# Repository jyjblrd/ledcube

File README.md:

# ledcube
Details: [https://www.joshuabird.com/blog/post/rgb-led-cube](https://www.joshuabird.com/blog/post/rgb-led-cube)

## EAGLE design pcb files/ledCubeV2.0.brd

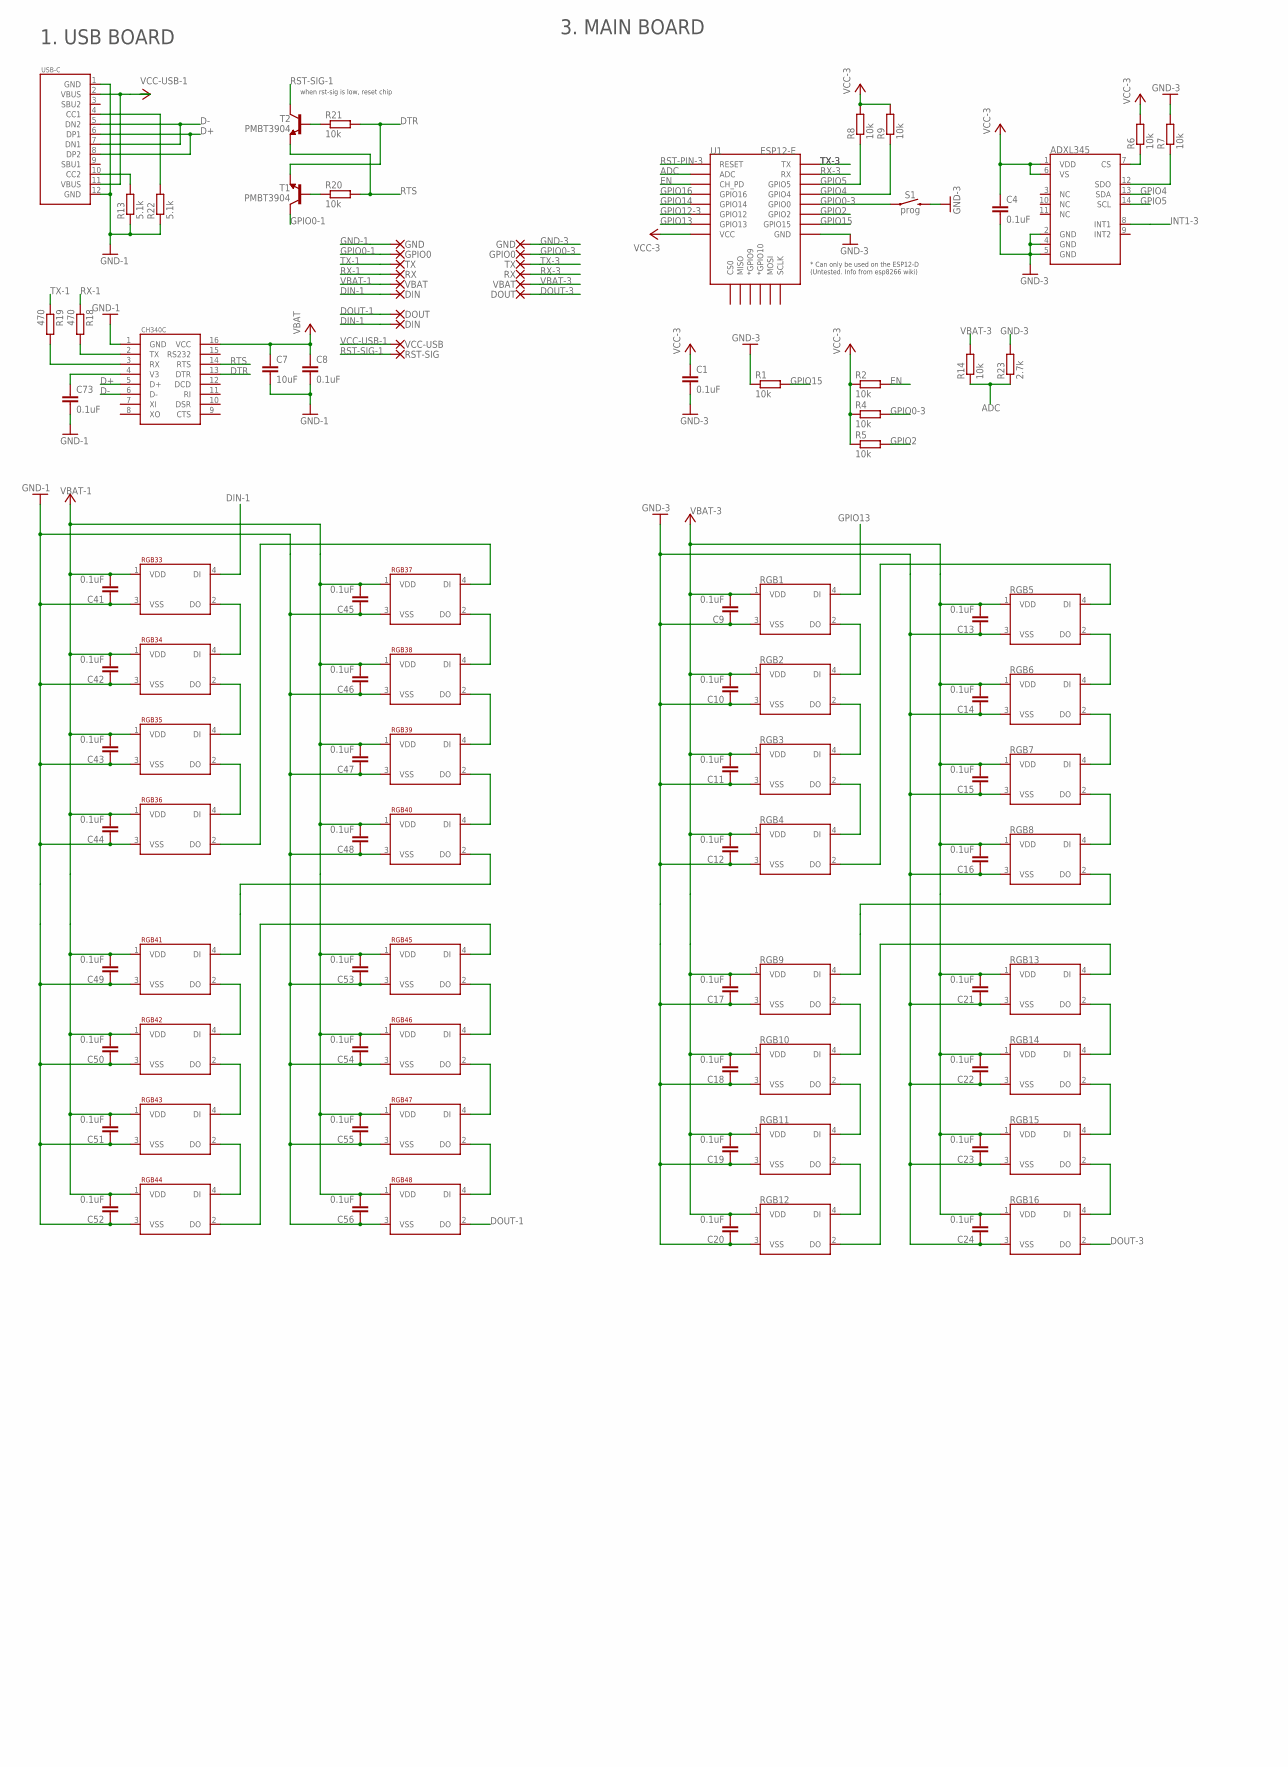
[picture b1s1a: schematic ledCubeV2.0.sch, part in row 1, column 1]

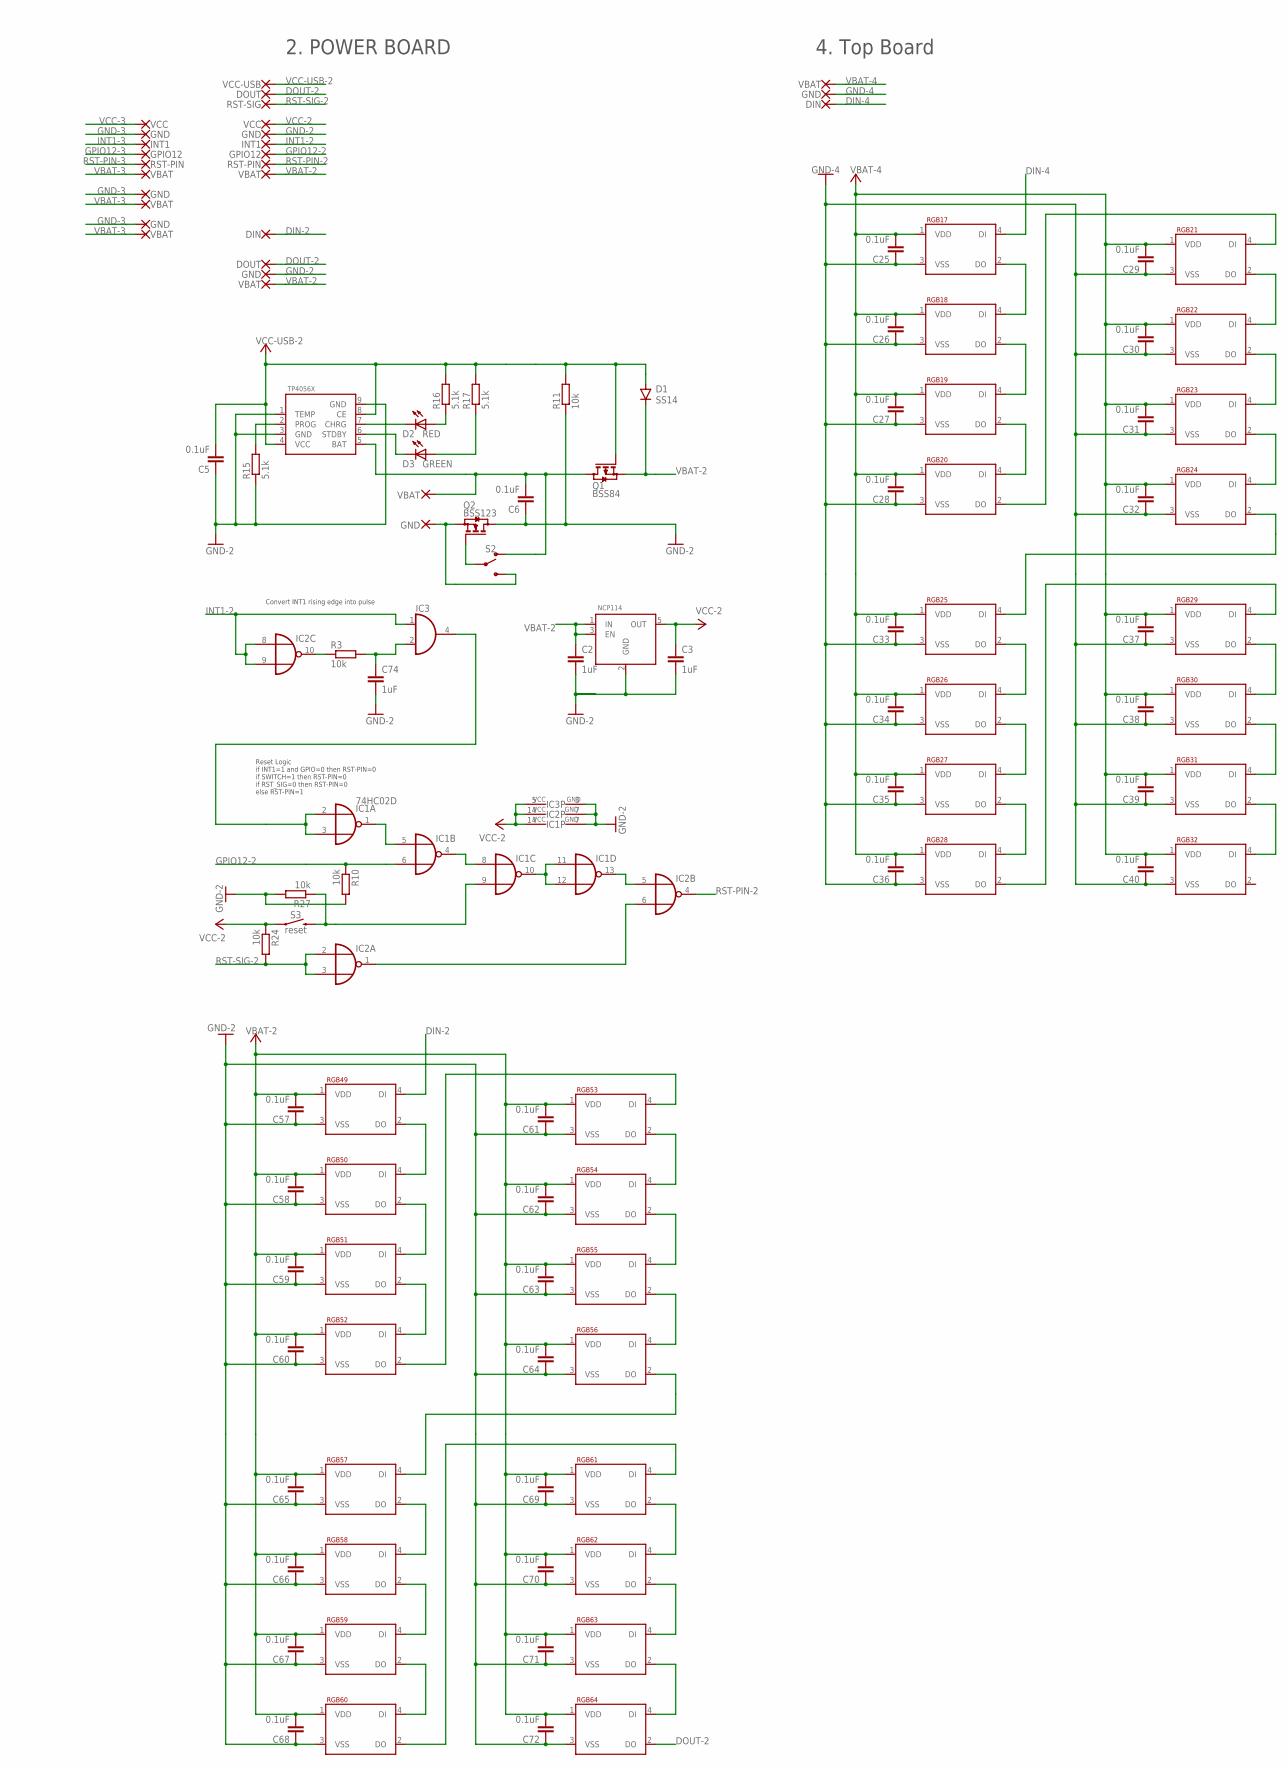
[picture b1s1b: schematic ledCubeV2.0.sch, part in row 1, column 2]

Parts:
ADXL345: ADXL345; LGA-14
C1, C4, C5, C6, C8, C9, C10, C11, C12, C13, C14, C15, C16, C17, C18, C19, C20, C21, C22, C23, C24, C25, C26, C27, C28, C29, C30, C31, C32, C33, C34, C35, C36, C37, C38, C39, C40, C41, C42, C43, C44, C45, C46, C47, C48, C49, C50, C51, C52, C53, C54, C55, C56, C57, C58, C59, C60, C61, C62, C63, C64, C65, C66, C67, C68, C69, C70, C71, C72, C73: 0.1uF; C0603
C2, C3, C74: 1uF; C0603
C7: 10uF; C0603
CH340C: CH340G; SOIC16
D1: SS14; DO-214AC
D2: RED; LED_SML0603
D3: GREEN; LED_SML0603
GND: SMD2; SMD1,27-2,54
GND-1: GND; SMD1,27-2,54
GND-2: RX; SMD1,27-2,54
GPIO0-1, GPIO0-2: GPIO0; SMD1,27-2,54
IC1, IC2: 74HC02D; SO14
IC3: 74AHC1G08DCK; SC70-5
NCP114: NCP114; TSOP-5
Q1: BSS84; SOT23
Q2: BSS123; SOT23
R1, R2, R3, R4, R5, R6, R7, R8, R9, R10, R11, R14, R20, R21, R24, R27: 10k; R0603
R13, R15, R16, R17, R22: 5.1k; R0603
R18, R19: 470; R0603
R23: 2.7k; R0603
RGB1, RGB2, RGB3, RGB4, RGB5, RGB6, RGB7, RGB8, RGB9, RGB10, RGB11, RGB12, RGB13, RGB14, RGB15, RGB16, RGB17, RGB18, RGB19, RGB20, RGB21, RGB22, RGB23, RGB24, RGB25, RGB26, RGB27, RGB28, RGB29, RGB30, RGB31, RGB32, RGB33, RGB34, RGB35, RGB36, RGB37, RGB38, RGB39, RGB40, RGB41, RGB42, RGB43, RGB44, RGB45, RGB46, RGB47, RGB48, RGB49, RGB50, RGB51, RGB52, RGB53, RGB54, RGB55, RGB56, RGB57, RGB58, RGB59, RGB60, RGB61, RGB62, RGB63, RGB64: WS2812B; WS2812B-MINI
RST-SIG-1: RST-SIG; SMD1,27-2,54
RST-SIG-2: TX; SMD1,27-2,54
RX-1: RX; SMD1,27-2,54
RX-2, RX-3: GND; SMD1,27-2,54
S1: prog; TACTILE_SWITCH_SMD_6.0X3.5MM
S2: ON/CHRG; SWITCH_SPST_SMD_A
S3: reset; TACTILE_SWITCH_SMD_6.0X3.5MM
T1, T2: PMBT3904; SOT23-BEC
TP4056X: TP4056X; ESPO8
TX-1: TX; SMD1,27-2,54
TX-3: DIN; SMD1,27-2,54
U1: ESP12-E; ESP12E-SMD
USB-C: USB-C
VBAT: SMD2; SMD1,27-2,54
VCC1, VCC2, VCC3, VCC4, VCC5, VCC6: VBAT; SMD1,27-2,54
VCC-USB-1, VCC-USB-3: VBAT; SMD1,27-2,54
VCC-USB-4, VCC-USB-7, VCC-USB-9: DIN; SMD1,27-2,54
VCC-USB-5, VCC-USB-6, VCC-USB-8, VCC-USB-15: DOUT; SMD1,27-2,54
VCC-USB-10, VCC-USB-13, VCC-USB-19, VCC-USB-25, VCC-USB-26: GND; SMD1,27-2,54
VCC-USB-11, VCC-USB-21: VCC; SMD1,27-2,54
VCC-USB-12, VCC-USB-22: INT1; SMD1,27-2,54
VCC-USB-14, VCC-USB-20: VCC-USB; SMD1,27-2,54
VCC-USB-16: RST-SIG; SMD1,27-2,54
VCC-USB-17, VCC-USB-23: GPIO12; SMD1,27-2,54
VCC-USB-18, VCC-USB-24: RST-PIN; SMD1,27-2,54

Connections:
ADC: R14.1, R23.1, U1.ADC
D+: CH340C.5 (D+), USB-C.6 (DP1), USB-C.8 (DP2)
D-: CH340C.6 (D-), USB-C.5 (DN2), USB-C.7 (DN1)
DIN-1: RGB33.4 (DI), VCC-USB-4.1, VCC-USB-7.1
DIN-2: RGB49.4 (DI), VCC-USB-9.1
DIN-4: RGB17.4 (DI), TX-3.1
DOUT-1: RGB48.2 (DO), VCC-USB-6.1
DOUT-2: RGB64.2 (DO), VCC-USB-8.1, VCC-USB-15.1
DOUT-3: RGB16.2 (DO), VCC-USB-5.1
DTR: CH340C.13 (DTR), R21.2, T1.E
EN: R2.2, U1.CH_PD
GND-1: C7.2, C8.2, C41.1, C42.1, C43.1, C44.1, C45.1, C46.1, C47.1, C48.1, C49.1, C50.1, C51.1, C52.1, C53.1, C54.1, C55.1, C56.1, C73.2, CH340C.1 (GND), GND-1.1, R13.1, R22.1, RGB33.3 (VSS), RGB34.3 (VSS), RGB35.3 (VSS), RGB36.3 (VSS), RGB37.3 (VSS), RGB38.3 (VSS), RGB39.3 (VSS), RGB40.3 (VSS), RGB41.3 (VSS), RGB42.3 (VSS), RGB43.3 (VSS), RGB44.3 (VSS), RGB45.3 (VSS), RGB46.3 (VSS), RGB47.3 (VSS), RGB48.3 (VSS), USB-C.1 (GND), USB-C.12 (GND)
GND-2: C2.2, C3.2, C5.1, C6.1, C57.1, C58.1, C59.1, C60.1, C61.1, C62.1, C63.1, C64.1, C65.1, C66.1, C67.1, C68.1, C69.1, C70.1, C71.1, C72.1, C74.2, IC1.7 (GND), IC2.7 (GND), IC3.3 (GND), NCP114.2 (GND), Q2.3 (D), R10.2, R11.1, R15.1, R27.2, RGB49.3 (VSS), RGB50.3 (VSS), RGB51.3 (VSS), RGB52.3 (VSS), RGB53.3 (VSS), RGB54.3 (VSS), RGB55.3 (VSS), RGB56.3 (VSS), RGB57.3 (VSS), RGB58.3 (VSS), RGB59.3 (VSS), RGB60.3 (VSS), RGB61.3 (VSS), RGB62.3 (VSS), RGB63.3 (VSS), RGB64.3 (VSS), TP4056X.1 (TEMP), TP4056X.3 (GND), TP4056X.9 (GND), VCC-USB-10.1, VCC-USB-19.1
GND-3: ADXL345.2 (GND), ADXL345.4 (GND), ADXL345.5 (GND), C1.2, C4.2, C9.1, C10.1, C11.1, C12.1, C13.1, C14.1, C15.1, C16.1, C17.1, C18.1, C19.1, C20.1, C21.1, C22.1, C23.1, C24.1, R1.1, R7.2, R23.2, RGB1.3 (VSS), RGB2.3 (VSS), RGB3.3 (VSS), RGB4.3 (VSS), RGB5.3 (VSS), RGB6.3 (VSS), RGB7.3 (VSS), RGB8.3 (VSS), RGB9.3 (VSS), RGB10.3 (VSS), RGB11.3 (VSS), RGB12.3 (VSS), RGB13.3 (VSS), RGB14.3 (VSS), RGB15.3 (VSS), RGB16.3 (VSS), RX-2.1, S1.2, U1.GND, VCC-USB-13.1, VCC-USB-25.1, VCC-USB-26.1
GND-4: C25.1, C26.1, C27.1, C28.1, C29.1, C30.1, C31.1, C32.1, C33.1, C34.1, C35.1, C36.1, C37.1, C38.1, C39.1, C40.1, RGB17.3 (VSS), RGB18.3 (VSS), RGB19.3 (VSS), RGB20.3 (VSS), RGB21.3 (VSS), RGB22.3 (VSS), RGB23.3 (VSS), RGB24.3 (VSS), RGB25.3 (VSS), RGB26.3 (VSS), RGB27.3 (VSS), RGB28.3 (VSS), RGB29.3 (VSS), RGB30.3 (VSS), RGB31.3 (VSS), RGB32.3 (VSS), RX-3.1
GPIO0-1: GPIO0-1.1, T1.C
GPIO0-3: GPIO0-2.1, R4.2, S1.1, U1.GPIO0
GPIO2: R5.2, U1.GPIO2
GPIO4: ADXL345.13 (SDA), R9.1, U1.GPIO4
GPIO5: ADXL345.14 (SCL), R8.1, U1.GPIO5
GPIO12-2: IC1.6 (I1), R10.1, VCC-USB-17.1
GPIO12-3: U1.GPIO12, VCC-USB-23.1
GPIO13: RGB1.4 (DI), U1.GPIO13
GPIO14: U1.GPIO14
GPIO15: R1.2, U1.GPIO15
GPIO16: U1.GPIO16
INT1-2: IC2.8 (I0), IC2.9 (I1), IC3.1 (I0), VCC-USB-12.1
INT1-3: ADXL345.8 (INT1), VCC-USB-22.1
unnamed: RGB1.2 (DO), RGB2.4 (DI)
unnamed: CH340C.2 (TX), R18.2
unnamed: ADXL345.7 (CS), R6.1
unnamed: ADXL345.12 (SDO), R7.1
unnamed: R13.2, USB-C.10 (CC2)
unnamed: IC1.2 (I0), IC1.3 (I1), IC3.4 (O)
unnamed: R22.2, USB-C.4 (CC1)
unnamed: GND.1, Q2.2 (S), S2.3 (S)
unnamed: D2.C, TP4056X.7 (CHRG)
unnamed: D3.C, TP4056X.6 (STDBY)
unnamed: R15.2, TP4056X.2 (PROG)
unnamed: D2.A, R16.1
unnamed: D3.A, R17.1
unnamed: CH340C.3 (RX), R19.2
unnamed: C6.2, Q1.3 (D), S2.1 (O), TP4056X.5 (BAT), VBAT.1
unnamed: R20.1, T1.B
unnamed: RGB4.2 (DO), RGB5.4 (DI)
unnamed: RGB2.2 (DO), RGB3.4 (DI)
unnamed: R21.1, T2.B
unnamed: RGB3.2 (DO), RGB4.4 (DI)
unnamed: RGB5.2 (DO), RGB6.4 (DI)
unnamed: RGB6.2 (DO), RGB7.4 (DI)
unnamed: RGB7.2 (DO), RGB8.4 (DI)
unnamed: RGB8.2 (DO), RGB9.4 (DI)
unnamed: RGB9.2 (DO), RGB10.4 (DI)
unnamed: RGB10.2 (DO), RGB11.4 (DI)
unnamed: RGB11.2 (DO), RGB12.4 (DI)
unnamed: RGB12.2 (DO), RGB13.4 (DI)
unnamed: RGB13.2 (DO), RGB14.4 (DI)
unnamed: RGB14.2 (DO), RGB15.4 (DI)
unnamed: RGB15.2 (DO), RGB16.4 (DI)
unnamed: RGB20.2 (DO), RGB21.4 (DI)
unnamed: RGB17.2 (DO), RGB18.4 (DI)
unnamed: RGB18.2 (DO), RGB19.4 (DI)
unnamed: RGB19.2 (DO), RGB20.4 (DI)
unnamed: RGB21.2 (DO), RGB22.4 (DI)
unnamed: RGB22.2 (DO), RGB23.4 (DI)
unnamed: RGB23.2 (DO), RGB24.4 (DI)
unnamed: RGB24.2 (DO), RGB25.4 (DI)
unnamed: RGB25.2 (DO), RGB26.4 (DI)
unnamed: RGB26.2 (DO), RGB27.4 (DI)
unnamed: RGB27.2 (DO), RGB28.4 (DI)
unnamed: RGB28.2 (DO), RGB29.4 (DI)
unnamed: RGB29.2 (DO), RGB30.4 (DI)
unnamed: RGB30.2 (DO), RGB31.4 (DI)
unnamed: RGB31.2 (DO), RGB32.4 (DI)
unnamed: RGB36.2 (DO), RGB37.4 (DI)
unnamed: RGB33.2 (DO), RGB34.4 (DI)
unnamed: RGB34.2 (DO), RGB35.4 (DI)
unnamed: RGB35.2 (DO), RGB36.4 (DI)
unnamed: RGB37.2 (DO), RGB38.4 (DI)
unnamed: RGB38.2 (DO), RGB39.4 (DI)
unnamed: RGB39.2 (DO), RGB40.4 (DI)
unnamed: RGB40.2 (DO), RGB41.4 (DI)
unnamed: RGB41.2 (DO), RGB42.4 (DI)
unnamed: RGB42.2 (DO), RGB43.4 (DI)
unnamed: RGB43.2 (DO), RGB44.4 (DI)
unnamed: RGB44.2 (DO), RGB45.4 (DI)
unnamed: RGB45.2 (DO), RGB46.4 (DI)
unnamed: RGB46.2 (DO), RGB47.4 (DI)
unnamed: RGB47.2 (DO), RGB48.4 (DI)
unnamed: RGB52.2 (DO), RGB53.4 (DI)
unnamed: RGB49.2 (DO), RGB50.4 (DI)
unnamed: RGB50.2 (DO), RGB51.4 (DI)
unnamed: RGB51.2 (DO), RGB52.4 (DI)
unnamed: RGB53.2 (DO), RGB54.4 (DI)
unnamed: RGB54.2 (DO), RGB55.4 (DI)
unnamed: RGB55.2 (DO), RGB56.4 (DI)
unnamed: RGB56.2 (DO), RGB57.4 (DI)
unnamed: RGB57.2 (DO), RGB58.4 (DI)
unnamed: RGB58.2 (DO), RGB59.4 (DI)
unnamed: RGB59.2 (DO), RGB60.4 (DI)
unnamed: RGB60.2 (DO), RGB61.4 (DI)
unnamed: RGB61.2 (DO), RGB62.4 (DI)
unnamed: RGB62.2 (DO), RGB63.4 (DI)
unnamed: RGB63.2 (DO), RGB64.4 (DI)
unnamed: C73.1, CH340C.4 (V3)
unnamed: C74.1, IC3.2 (I1), R3.2
unnamed: IC1.9 (I1), R27.1, S3.2
unnamed: IC1.1 (O), IC1.5 (I0)
unnamed: IC1.10 (O), IC1.11 (I0), IC1.12 (I1)
unnamed: IC1.4 (O), IC1.8 (I0)
unnamed: IC2.1 (O), IC2.6 (I1)
unnamed: IC1.13 (O), IC2.5 (I0)
unnamed: IC2.10 (O), R3.1
unnamed: Q2.1 (G), S2.2
RST-PIN-2: IC2.4 (O), VCC-USB-18.1
RST-PIN-3: U1.RESET, VCC-USB-24.1
RST-SIG-1: RST-SIG-1.1, T2.C
RST-SIG-2: IC2.2 (I0), IC2.3 (I1), R24.2, VCC-USB-16.1
RTS: CH340C.14 (RTS), R20.2, T2.E
RX-1: R18.1, RX-1.1
RX-3: GND-2.1, U1.RXD0 (RX)
TX-1: R19.1, TX-1.1
TX-3: RST-SIG-2.1, U1.TXD0 (TX)
VBAT: C7.1, C8.1, CH340C.16 (VCC)
VBAT-1: C41.2, C42.2, C43.2, C44.2, C45.2, C46.2, C47.2, C48.2, C49.2, C50.2, C51.2, C52.2, C53.2, C54.2, C55.2, C56.2, RGB33.1 (VDD), RGB34.1 (VDD), RGB35.1 (VDD), RGB36.1 (VDD), RGB37.1 (VDD), RGB38.1 (VDD), RGB39.1 (VDD), RGB40.1 (VDD), RGB41.1 (VDD), RGB42.1 (VDD), RGB43.1 (VDD), RGB44.1 (VDD), RGB45.1 (VDD), RGB46.1 (VDD), RGB47.1 (VDD), RGB48.1 (VDD), VCC-USB-1.1
VBAT-2: C2.1, C57.2, C58.2, C59.2, C60.2, C61.2, C62.2, C63.2, C64.2, C65.2, C66.2, C67.2, C68.2, C69.2, C70.2, C71.2, C72.2, D1.C, NCP114.1 (IN), NCP114.3 (EN), Q1.2 (S), RGB49.1 (VDD), RGB50.1 (VDD), RGB51.1 (VDD), RGB52.1 (VDD), RGB53.1 (VDD), RGB54.1 (VDD), RGB55.1 (VDD), RGB56.1 (VDD), RGB57.1 (VDD), RGB58.1 (VDD), RGB59.1 (VDD), RGB60.1 (VDD), RGB61.1 (VDD), RGB62.1 (VDD), RGB63.1 (VDD), RGB64.1 (VDD), VCC2.1, VCC3.1
VBAT-3: C9.2, C10.2, C11.2, C12.2, C13.2, C14.2, C15.2, C16.2, C17.2, C18.2, C19.2, C20.2, C21.2, C22.2, C23.2, C24.2, R14.2, RGB1.1 (VDD), RGB2.1 (VDD), RGB3.1 (VDD), RGB4.1 (VDD), RGB5.1 (VDD), RGB6.1 (VDD), RGB7.1 (VDD), RGB8.1 (VDD), RGB9.1 (VDD), RGB10.1 (VDD), RGB11.1 (VDD), RGB12.1 (VDD), RGB13.1 (VDD), RGB14.1 (VDD), RGB15.1 (VDD), RGB16.1 (VDD), VCC1.1, VCC4.1, VCC5.1, VCC6.1
VBAT-4: C25.2, C26.2, C27.2, C28.2, C29.2, C30.2, C31.2, C32.2, C33.2, C34.2, C35.2, C36.2, C37.2, C38.2, C39.2, C40.2, RGB17.1 (VDD), RGB18.1 (VDD), RGB19.1 (VDD), RGB20.1 (VDD), RGB21.1 (VDD), RGB22.1 (VDD), RGB23.1 (VDD), RGB24.1 (VDD), RGB25.1 (VDD), RGB26.1 (VDD), RGB27.1 (VDD), RGB28.1 (VDD), RGB29.1 (VDD), RGB30.1 (VDD), RGB31.1 (VDD), RGB32.1 (VDD), VCC-USB-3.1
VCC-2: C3.1, IC1.14 (VCC), IC2.14 (VCC), IC3.5 (VCC), NCP114.5 (OUT), R24.1, S3.1, VCC-USB-11.1
VCC-3: ADXL345.1 (VDD), ADXL345.6 (VS), C1.1, C4.1, R2.1, R4.1, R5.1, R6.2, R8.2, R9.2, U1.VCC, VCC-USB-21.1
VCC-USB-1: USB-C.2 (VBUS), USB-C.11 (VBUS), VCC-USB-14.1
VCC-USB-2: C5.2, D1.A, Q1.1 (G), R11.2, R16.2, R17.2, TP4056X.4 (VCC), TP4056X.8 (CE), VCC-USB-20.1

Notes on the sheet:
when rst-sig is low, reset chip
Reset Logic if INT1=1 and GPIO=0 then RST-PIN=0 if SWITCH=1 then RST-PIN=0 if RST_SIG=0 then RST-PIN=0 else RST-PIN=1
3. MAIN BOARD
2. POWER BOARD
1. USB BOARD
4. Top Board
Convert INT1 rising edge into pulse

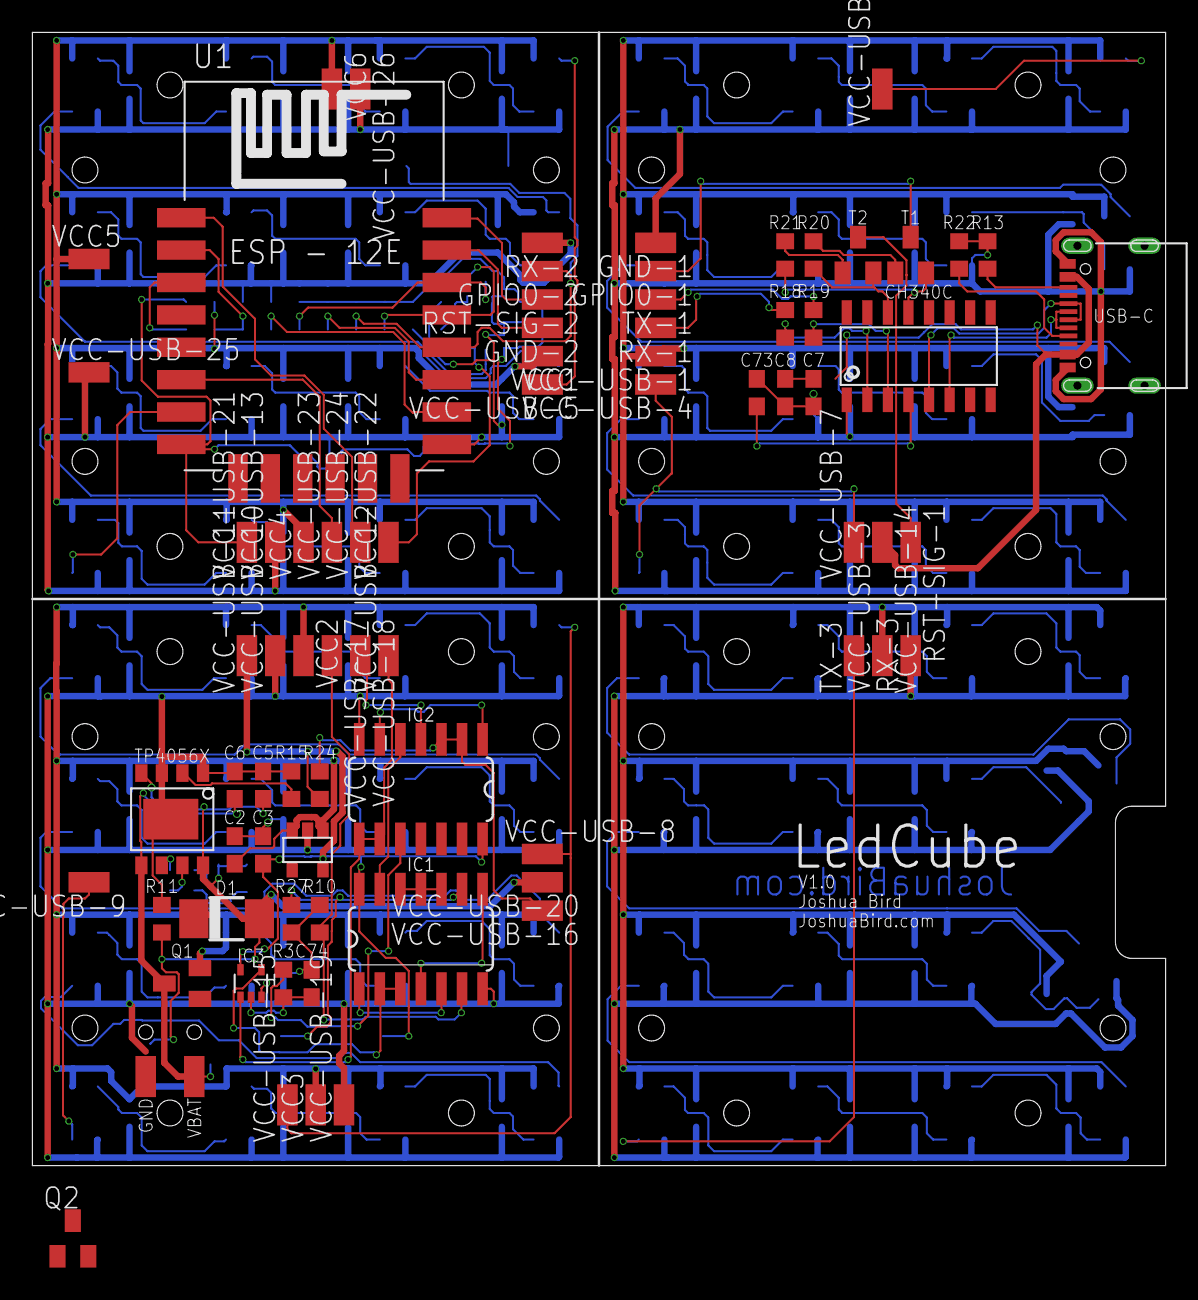
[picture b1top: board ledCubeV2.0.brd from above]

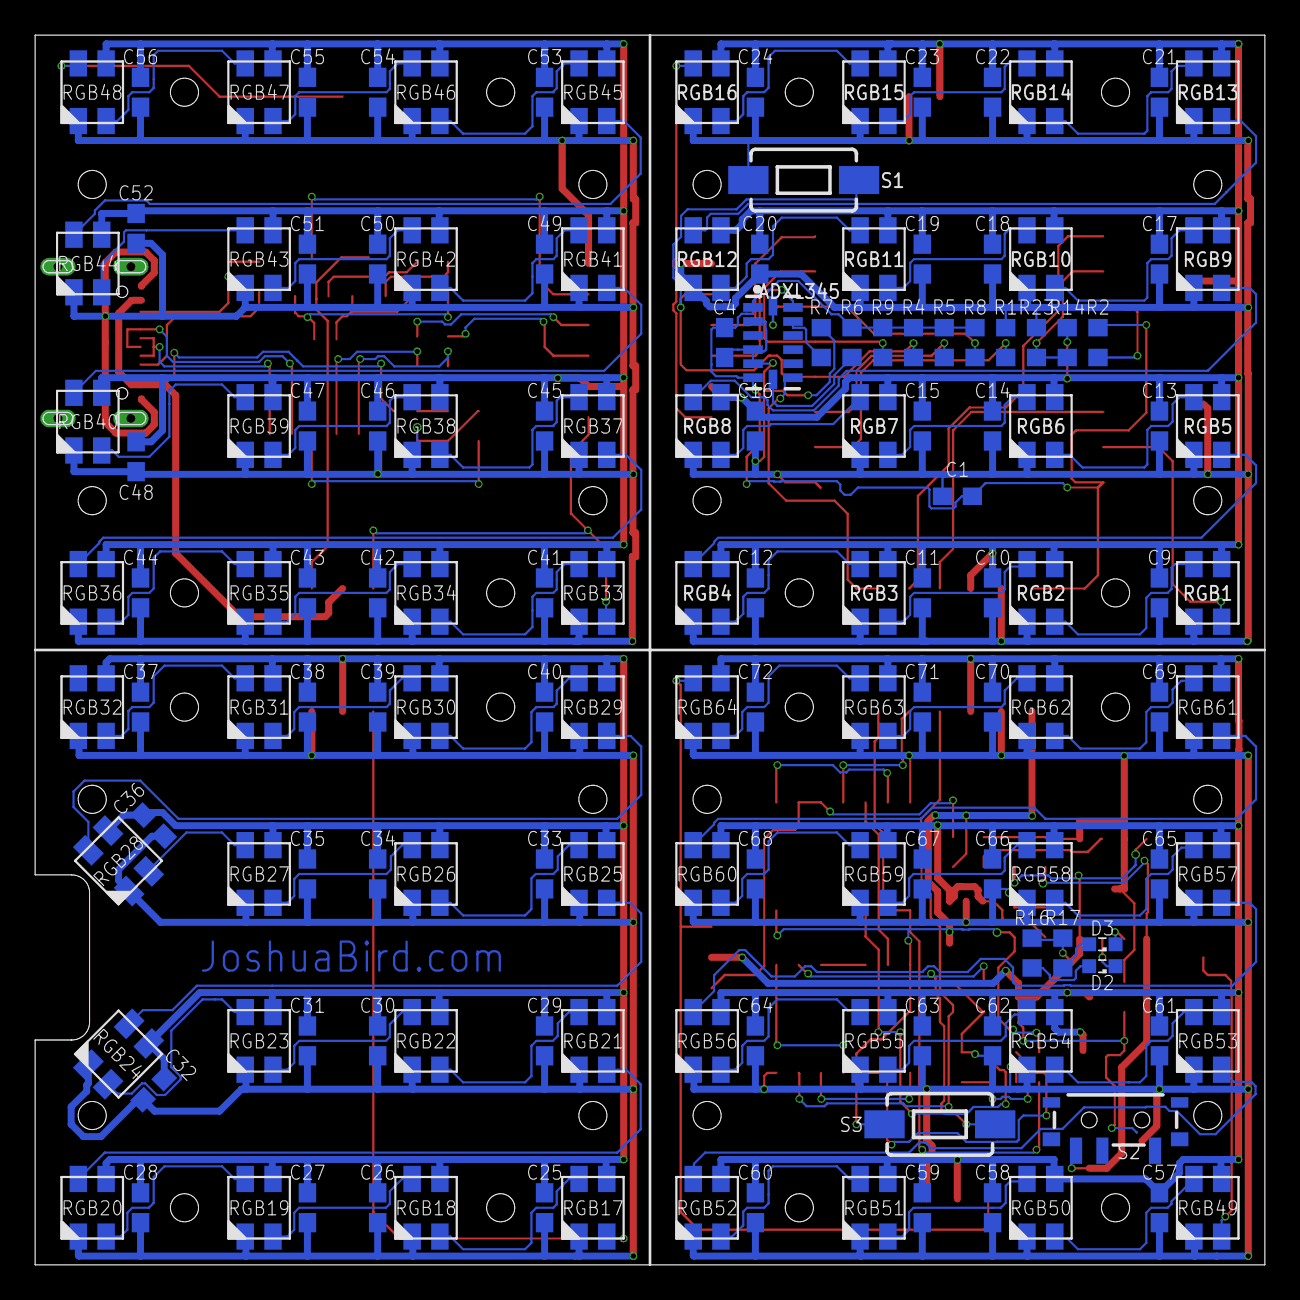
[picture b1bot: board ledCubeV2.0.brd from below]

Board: 2 copper layers, 70.0 x 70.0 mm, 225 parts (148 on the bottom side), 130 nets.

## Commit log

2021-04-03 init commit
2021-04-03 more stuff
2021-04-03 pcb files

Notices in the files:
parts and their libraries:
SparkFun-Switches: Licensing: Creative Commons ShareAlike 4.0 International - https://creativecommons.org/licenses/by-sa/4.0
